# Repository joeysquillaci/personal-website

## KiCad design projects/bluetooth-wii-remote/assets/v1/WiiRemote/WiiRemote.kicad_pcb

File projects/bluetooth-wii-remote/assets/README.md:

# ESP32 Air Pointer

A Wii Remote–style Bluetooth air mouse built using an ESP32 and an Adafruit BNO055 9-axis IMU.

The device tracks controller orientation in space and presents itself to a computer as a Bluetooth HID mouse. Controller yaw and pitch are mapped to a virtual cursor position, allowing the user to point at the screen by physically aiming the controller.

Additional directional buttons provide manual cursor panning for fine adjustment and navigation.

---

## Features

- Bluetooth HID mouse using ESP32 BLE
- BNO055 sensor fusion for absolute orientation tracking
- Wii Remote–style pointing behavior
- Yaw controls horizontal cursor movement
- Pitch controls vertical cursor movement
- Deadzone filtering to reduce jitter
- Low-pass filtering for smoother movement
- Automatic rejection of large orientation glitches
- Manual recentering via serial command
- Directional button panning
- Virtual cursor tracking to approximate absolute positioning
- Artificial software cursor bounds removed to prevent early edge clipping

---

## Hardware

### Main Components

- ESP32 development board
- Adafruit BNO055 9-axis IMU
- 3.7V Li-Ion battery
- Li-Ion charging module
- Buck/boost converter
- Four directional buttons

### BNO055 Wiring

| BNO055 | ESP32 |
|----------|----------|
| VIN | 3.3V |
| GND | GND |
| SDA | GPIO21 |
| SCL | GPIO22 |

I²C configuration:

```cpp
Wire.begin(21, 22);
Wire.setClock(400000);
```

BNO055 I²C address:

```cpp
0x28
```

### Directional Buttons

| Function | ESP32 Pin |
|-----------|-----------|
| Up | GPIO13 |
| Down | GPIO14 |
| Left | GPIO27 |
| Right | GPIO26 |

Buttons are configured using INPUT_PULLUP and connect to GND when pressed.

---

## Bluetooth

Device Name:

```text
ESP32 Air Pointer
```

Manufacturer:

```text
Joey
```

The device appears as a standard Bluetooth HID mouse.

---

## Cursor Mapping

The controller operates as a virtual absolute pointer:

1. Orientation is read from the BNO055.
2. Relative yaw and pitch are calculated.
3. Angles are converted into a target screen position.
4. The cursor continuously moves toward that target.

This produces behavior similar to a Wii Remote.

### Horizontal Mapping

```cpp
yawEdgeDeg = 60.0;
```

### Vertical Mapping

```cpp
pitchEdgeDeg = 33.0;
```

Vertical movement is intentionally more sensitive than horizontal movement.

---

## Filtering

### Deadzone

```cpp
yawDeadzoneDeg = 0.4;
pitchDeadzoneDeg = 0.4;
```

### Low Pass Filter

```cpp
angleSmoothing = 0.18;
```

Lower values increase smoothness. Higher values increase responsiveness.

### Yaw Jump Rejection

Large orientation discontinuities are ignored.

Example:

```text
20° -> 130°
```

Threshold:

```cpp
maxYawJumpDeg = 35.0;
```

---

## Cursor Tuning

```cpp
followGain = 0.11;
maxMoveStep = 18;
virtualMovementScale = 0.45;
```

These values control responsiveness and compensate for operating-system mouse acceleration.

---

## Button Panning

Directional buttons continuously shift the target position while held.

```cpp
buttonPanStep = 4.0;
```

This allows fine adjustment without changing controller orientation.

---

## Recentering

To recenter:

1. Aim the controller where you want screen center.
2. Open Serial Monitor.
3. Send:

```text
c
```

The software will:
- Reset yaw and pitch references
- Reset button offsets
- Move the cursor back to screen center

---

## Known Limitations

### Virtual Cursor Tracking

The ESP32 cannot read the actual host cursor position.

Instead it maintains an internal estimate using:

```cpp
virtualX
virtualY
```

Because of this:

- Minor drift can accumulate
- Mouse acceleration affects accuracy
- Periodic recentering may be required

### BNO055 Yaw Stability

The BNO055 occasionally produces sudden yaw discontinuities. Filtering reduces their impact but cannot eliminate them completely.

---

## Future Improvements

- Left/right click buttons
- Scroll wheel emulation
- Battery monitoring
- Automatic drift compensation
- Host-side cursor synchronization
- IR beacon tracking similar to the original Wii Remote
- Custom BLE HID implementation

---

## Tuned Parameters

```cpp
yawEdgeDeg            = 60.0
pitchEdgeDeg          = 33.0

yawDeadzoneDeg        = 0.4
pitchDeadzoneDeg      = 0.4

maxYawJumpDeg         = 35.0
maxPitchJumpDeg       = 35.0

angleSmoothing        = 0.18

followGain            = 0.11
maxMoveStep           = 18

virtualMovementScale  = 0.45

buttonPanStep         = 4.0

updateMs              = 5
```

These values were tuned on a 3440×1440 ultrawide display running macOS.

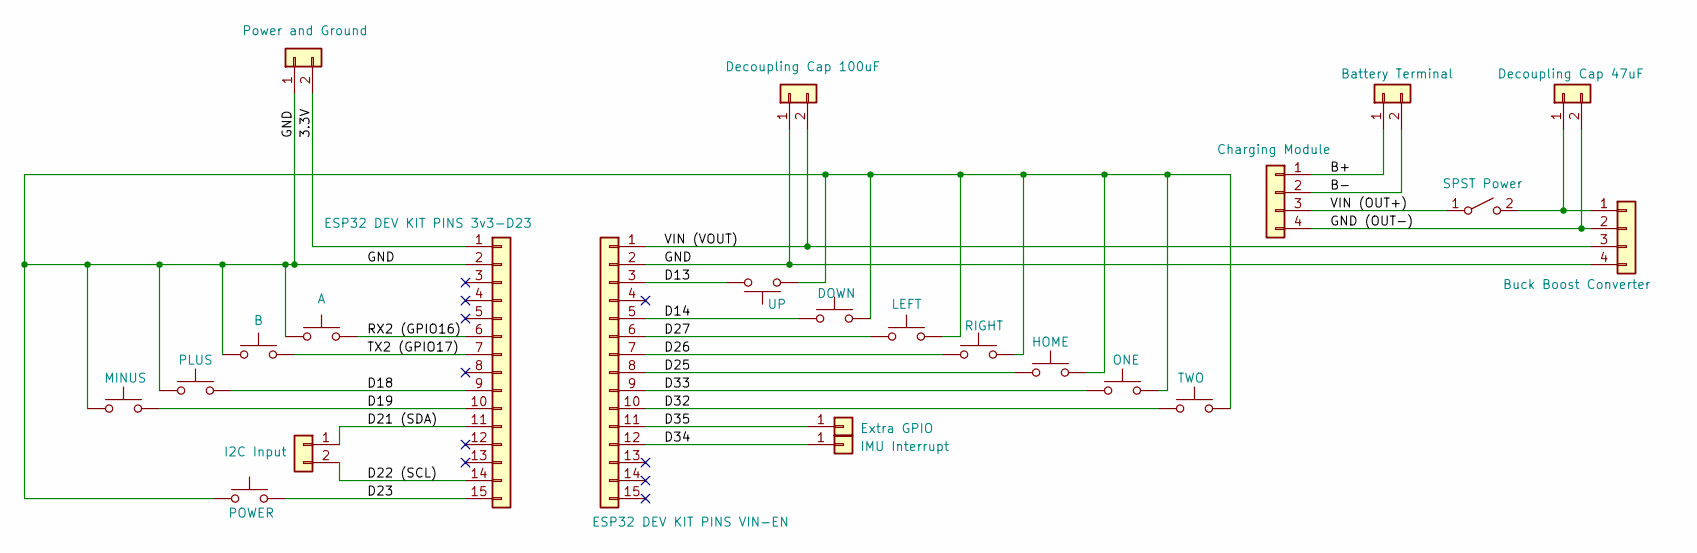
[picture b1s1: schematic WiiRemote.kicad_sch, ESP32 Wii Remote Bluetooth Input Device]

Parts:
Conn_01x01_EXTRA_GPIO0: Extra GPIO; PinSocket_1x01_P2.54mm_Vertical
Conn_01x01_IMU_INTERRUPT0: IMU Interrupt; PinSocket_1x01_P2.54mm_Vertical
Conn_01x02_DECOUPLING_CAP_100uF0: Decoupling Cap 100uF; PinSocket_1x02_P2.54mm_Vertical
Conn_01x02_I2C_INPUT0: I2C Input; PinSocket_1x02_P2.54mm_Vertical
Conn_01x02_POWER_AND_GROUND0: Power and Ground; PinSocket_1x02_P2.54mm_Vertical
Conn_01x02_battery_terminal0: Battery Terminal; PinSocket_1x02_P2.54mm_Vertical
Conn_01x04_BUCKBOOST0: Buck Boost Converter; BuckBoostConverter
Conn_01x04_CHARGING_MODULE0: Charging Module; TP4056
Conn_01x15_ESP32_DEV_KIT_PINS_3v3-D230: ESP32 DEV KIT PINS 3v3-D23; PinSocket_1x15_P2.54mm_Vertical
Conn_01x15_ESP32_DEV_KIT_PINS_VIN-EN0: ESP32 DEV KIT PINS VIN-EN; PinSocket_1x15_P2.54mm_Vertical
DECOUPLING_CAP_47uF0: Decoupling Cap 47uF; PinSocket_1x02_P2.54mm_Vertical
SPST_POWER_SWITCH0: SPST Power; SW_DIP_SPSTx01_Slide_9.78x4.72mm_W8.61mm_P2.54mm
SW_Push0: A; Button SMD 5x5mm
SW_Push1: B; Button SMD 5x5mm
SW_Push2: PLUS; Button SMD 5x5mm
SW_Push3: MINUS; Button SMD 5x5mm
SW_Push4: POWER; Button SMD 5x5mm
SW_Push5: UP; Button SMD 5x5mm
SW_Push6: DOWN; Button SMD 5x5mm
SW_Push7: LEFT; Button SMD 5x5mm
SW_Push8: RIGHT; Button SMD 5x5mm
SW_Push9: HOME; Button SMD 5x5mm
SW_Push10: ONE; Button SMD 5x5mm
SW_Push11: TWO; Button SMD 5x5mm

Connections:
/3.3V: Conn_01x02_POWER_AND_GROUND0.2, Conn_01x15_ESP32_DEV_KIT_PINS_3v3-D230.1
/B+: Conn_01x02_battery_terminal0.1, Conn_01x04_CHARGING_MODULE0.1
/B-: Conn_01x02_battery_terminal0.2, Conn_01x04_CHARGING_MODULE0.2
/D13: Conn_01x15_ESP32_DEV_KIT_PINS_VIN-EN0.3, SW_Push5.1
/D14: Conn_01x15_ESP32_DEV_KIT_PINS_VIN-EN0.5, SW_Push6.1
/D18: Conn_01x15_ESP32_DEV_KIT_PINS_3v3-D230.9, SW_Push2.2
/D19: Conn_01x15_ESP32_DEV_KIT_PINS_3v3-D230.10, SW_Push3.2
/D21 (SDA): Conn_01x02_I2C_INPUT0.1, Conn_01x15_ESP32_DEV_KIT_PINS_3v3-D230.11
/D22 (SCL): Conn_01x02_I2C_INPUT0.2, Conn_01x15_ESP32_DEV_KIT_PINS_3v3-D230.14
/D23: Conn_01x15_ESP32_DEV_KIT_PINS_3v3-D230.15, SW_Push4.2
/D25: Conn_01x15_ESP32_DEV_KIT_PINS_VIN-EN0.8, SW_Push9.1
/D26: Conn_01x15_ESP32_DEV_KIT_PINS_VIN-EN0.7, SW_Push8.1
/D27: Conn_01x15_ESP32_DEV_KIT_PINS_VIN-EN0.6, SW_Push7.1
/D32: Conn_01x15_ESP32_DEV_KIT_PINS_VIN-EN0.10, SW_Push11.1
/D33: Conn_01x15_ESP32_DEV_KIT_PINS_VIN-EN0.9, SW_Push10.1
/D34: Conn_01x01_IMU_INTERRUPT0.1 (Pin_1_1), Conn_01x15_ESP32_DEV_KIT_PINS_VIN-EN0.12
/D35: Conn_01x01_EXTRA_GPIO0.1 (Pin_1_1), Conn_01x15_ESP32_DEV_KIT_PINS_VIN-EN0.11
/GND: Conn_01x02_DECOUPLING_CAP_100uF0.1, Conn_01x02_POWER_AND_GROUND0.1, Conn_01x04_BUCKBOOST0.4, Conn_01x15_ESP32_DEV_KIT_PINS_3v3-D230.2, Conn_01x15_ESP32_DEV_KIT_PINS_VIN-EN0.2, SW_Push0.1, SW_Push1.1, SW_Push2.1, SW_Push3.1, SW_Push4.1, SW_Push5.2, SW_Push6.2, SW_Push7.2, SW_Push8.2, SW_Push9.2, SW_Push10.2, SW_Push11.2
/GND (OUT-): Conn_01x04_BUCKBOOST0.2, Conn_01x04_CHARGING_MODULE0.4, DECOUPLING_CAP_47uF0.2
/RX2 (GPIO16): Conn_01x15_ESP32_DEV_KIT_PINS_3v3-D230.6, SW_Push0.2
/TX2 (GPIO17): Conn_01x15_ESP32_DEV_KIT_PINS_3v3-D230.7, SW_Push1.2
/VIN (OUT+): Conn_01x04_CHARGING_MODULE0.3, SPST_POWER_SWITCH0.1 (A)
/VIN (VOUT): Conn_01x02_DECOUPLING_CAP_100uF0.2, Conn_01x04_BUCKBOOST0.3, Conn_01x15_ESP32_DEV_KIT_PINS_VIN-EN0.1
unnamed: Conn_01x04_BUCKBOOST0.1, DECOUPLING_CAP_47uF0.1, SPST_POWER_SWITCH0.2 (B)

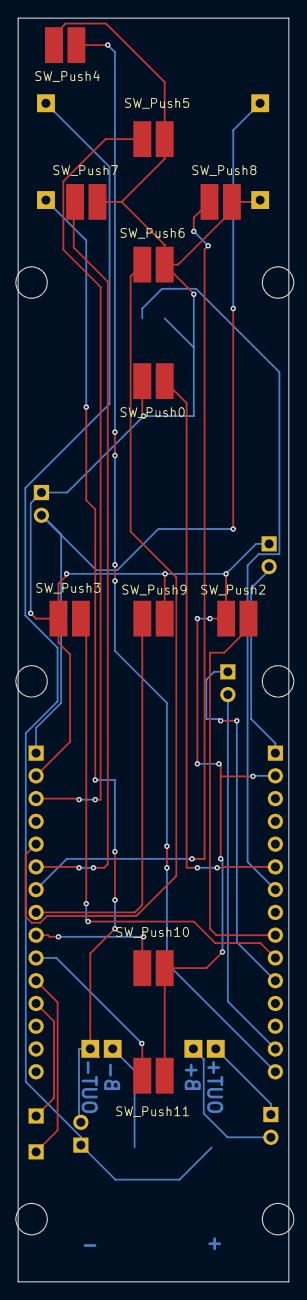
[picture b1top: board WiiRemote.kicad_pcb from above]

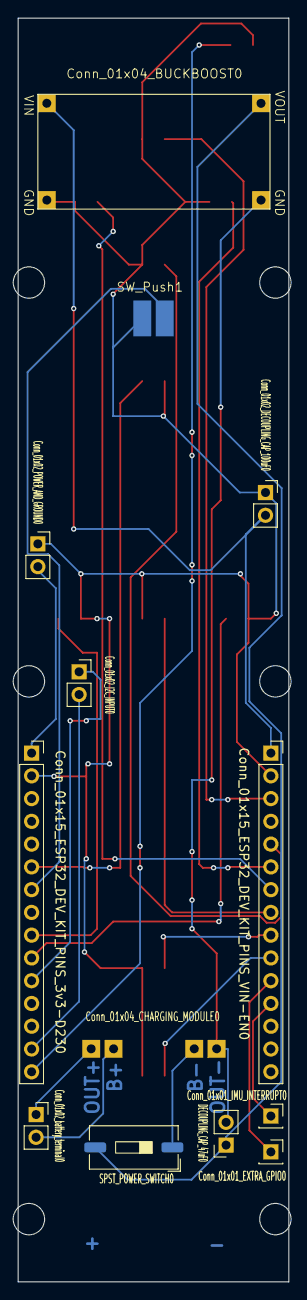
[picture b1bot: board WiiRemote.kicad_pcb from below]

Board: 2 copper layers, 30.2 x 141.0 mm, 24 parts (13 on the bottom side), 24 nets.

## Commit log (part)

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2026-04-21 Create CNAME
2026-04-21 Added CNAME file
2026-04-21 Update CNAME
2026-05-18 Added Options Hub Project
2026-05-18 Updated naming
2026-05-18 Updated resume
2026-06-06 Added Bluetooth Wii Remote Project
2026-06-06 Fixing styling
    For some reason pushing to Github didn't align the styling that was present on local machine, so updating files and trying again
